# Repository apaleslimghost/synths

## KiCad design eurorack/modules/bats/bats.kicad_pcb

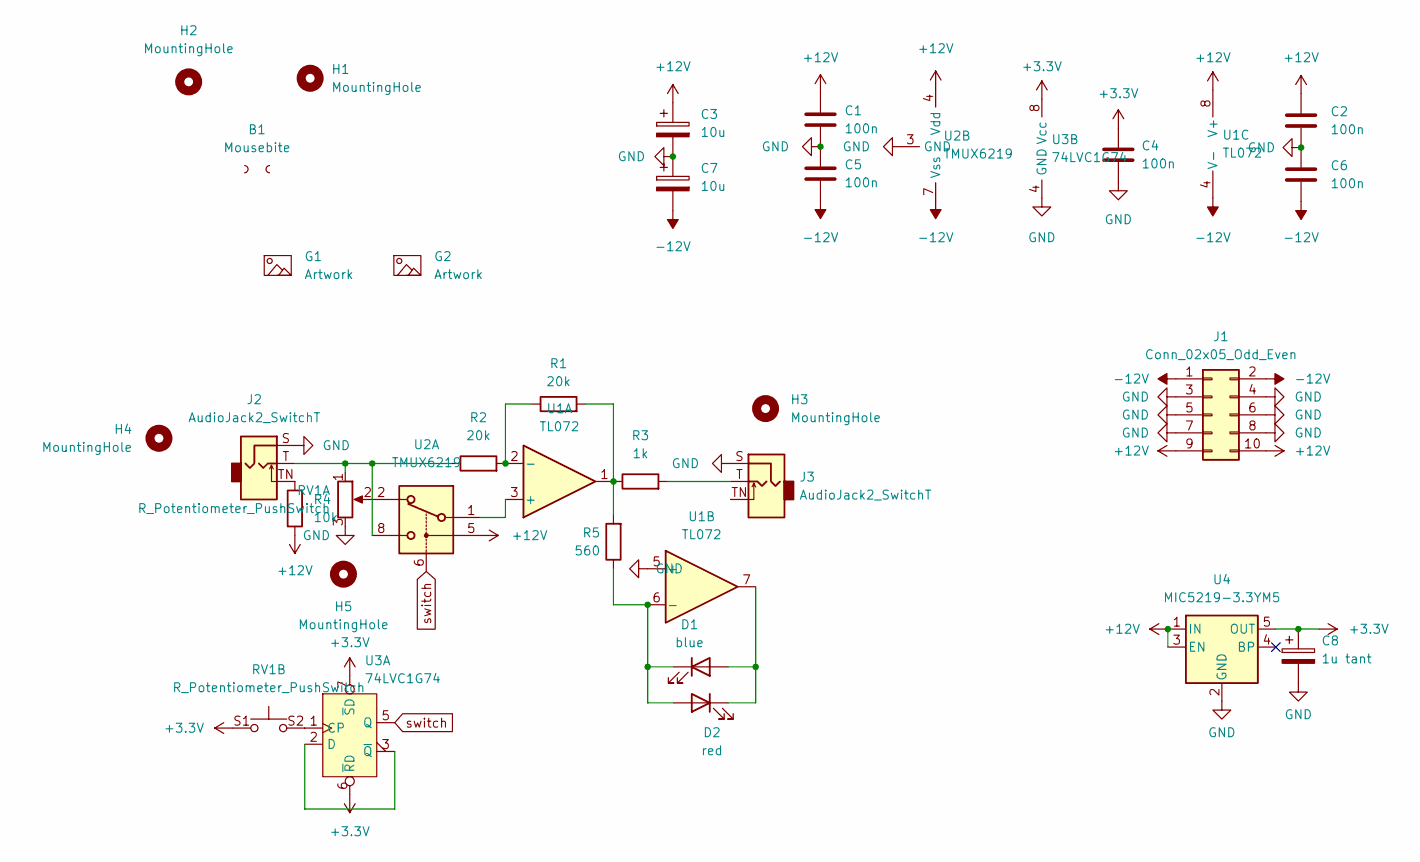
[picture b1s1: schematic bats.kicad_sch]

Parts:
B1: Mousebite; mousebite-2.54x5.08mm
C1, C2, C4, C5, C6: 100n; C_0805_2012Metric_Pad1.18x1.45mm_HandSolder
C3, C7: 10u; CP_EIA-3216-18_Kemet-A_Pad1.58x1.35mm_HandSolder
C8: 1u tant; CP_EIA-3216-18_Kemet-A_Pad1.58x1.35mm_HandSolder
D1: blue; LED_0805_2012Metric_Pad1.15x1.40mm_HandSolder
D2: red; LED_0805_2012Metric_Pad1.15x1.40mm_HandSolder
G1, G2: Artwork
H1, H2: MountingHole; eurorack panel mounting slot
H3, H4: MountingHole; hole 6mm (jack panel)
H5: MountingHole; hole 6.5mm (potentiometer panel)
J1: Conn_02x05_Odd_Even; PinHeader_2x05_P2.54mm_Vertical_SMD
J2, J3: AudioJack2_SwitchT; Jack_3.5mm_QingPu_WQP-PJ398SM_Vertical
R1, R2: 20k; R_0805_2012Metric_Pad1.20x1.40mm_HandSolder
R3: 1k; R_0805_2012Metric_Pad1.20x1.40mm_HandSolder
R4: 10k; R_0805_2012Metric_Pad1.20x1.40mm_HandSolder
R5: 560; R_0805_2012Metric_Pad1.20x1.40mm_HandSolder
RV1: R_Potentiometer_PushSwitch; PRS11R Momentary Switch Potentiometer; Part # P170SP1-QC15BR10K
U1: TL072; SOT-23-8_Handsoldering
U2: TMUX6219; VSSOP-8_3.0x3.0mm_P0.65mm
U3: 74LVC1G74; SSOP-8_2.95x2.8mm_P0.65mm
U4: MIC5219-3.3YM5; SOT-23-5

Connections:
+3.3V: C4.1, C8.1, RV1.S1, U3.6 (~RD), U3.7 (~SD), U3.8 (Vcc), U4.5 (OUT)
+12V: C1.1, C2.1, C3.1, J1.9, J1.10, R4.1, U1.8 (V+), U2.4 (Vdd), U2.5, U4.1 (IN), U4.3 (EN)
-12V: C5.2, C6.2, C7.2, J1.1, J1.2, U1.4 (V-), U2.7 (Vss)
GND: C1.2, C2.2, C3.2, C4.2, C5.1, C6.1, C7.1, C8.2, J1.3, J1.4, J1.5, J1.6, J1.7, J1.8, J2.S, J3.S, RV1.3, U1.5 (+), U2.3 (GND), U3.4 (GND), U4.2 (GND)
unnamed: D1.1 (K), D2.2 (A), R5.1, U1.6 (-)
unnamed: D1.2 (A), D2.1 (K), U1.7
unnamed: J2.T, R2.1, RV1.1, U2.8
unnamed: J2.TN, R4.2
unnamed: J3.T, R3.2
unnamed: R1.1, R2.2, U1.2 (-)
unnamed: R1.2, R3.1, R5.2, U1.1
unnamed: RV1.2, U2.2
unnamed: RV1.S2, U3.1 (CP)
unnamed: U1.3 (+), U2.1
unnamed: U3.2 (D), U3.3 (~Q)
switch: U2.6, U3.5 (Q)

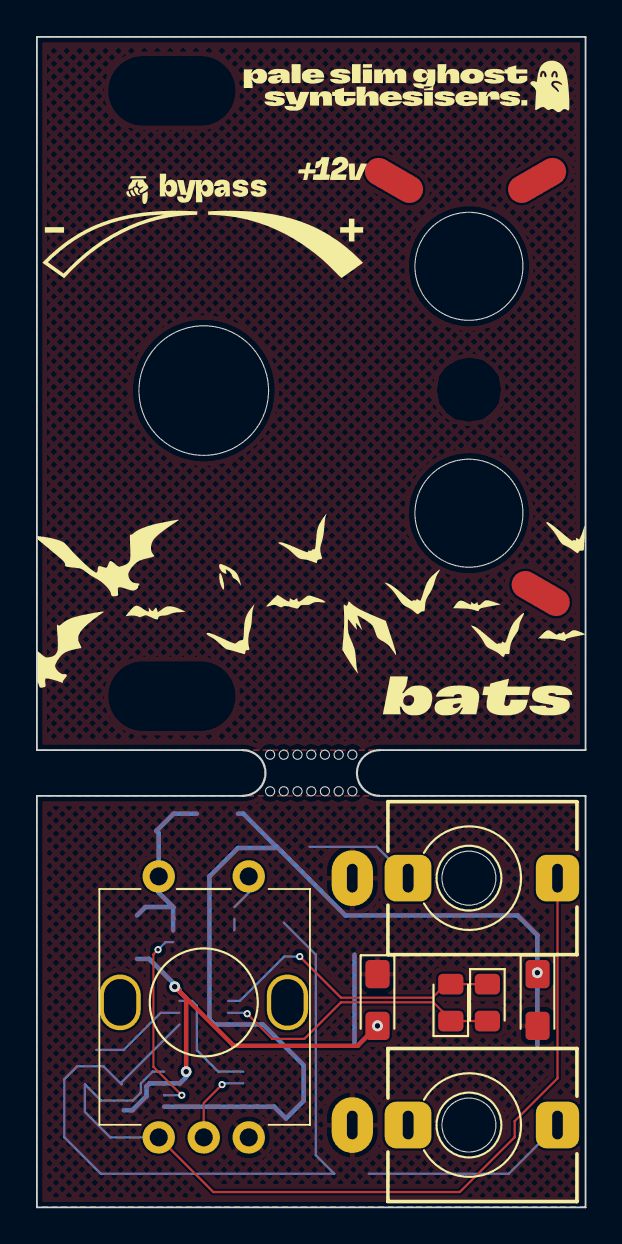
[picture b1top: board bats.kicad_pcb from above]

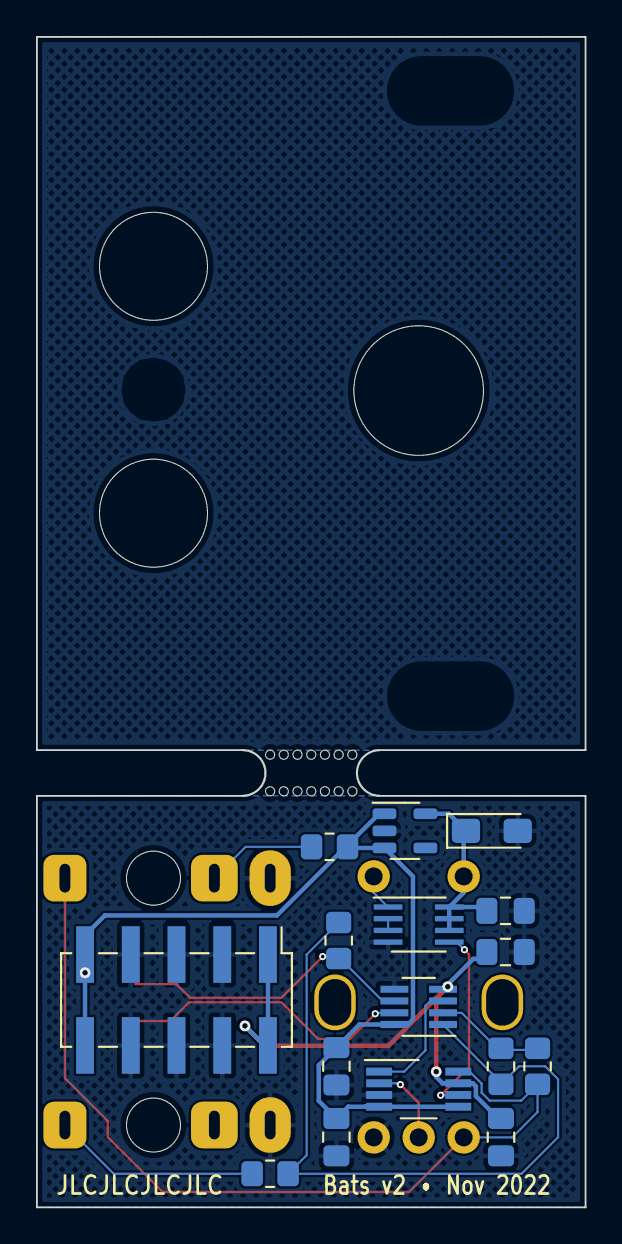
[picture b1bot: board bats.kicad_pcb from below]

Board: 2 copper layers, 30.5 x 65.0 mm, 31 parts (16 on the bottom side), 16 nets.

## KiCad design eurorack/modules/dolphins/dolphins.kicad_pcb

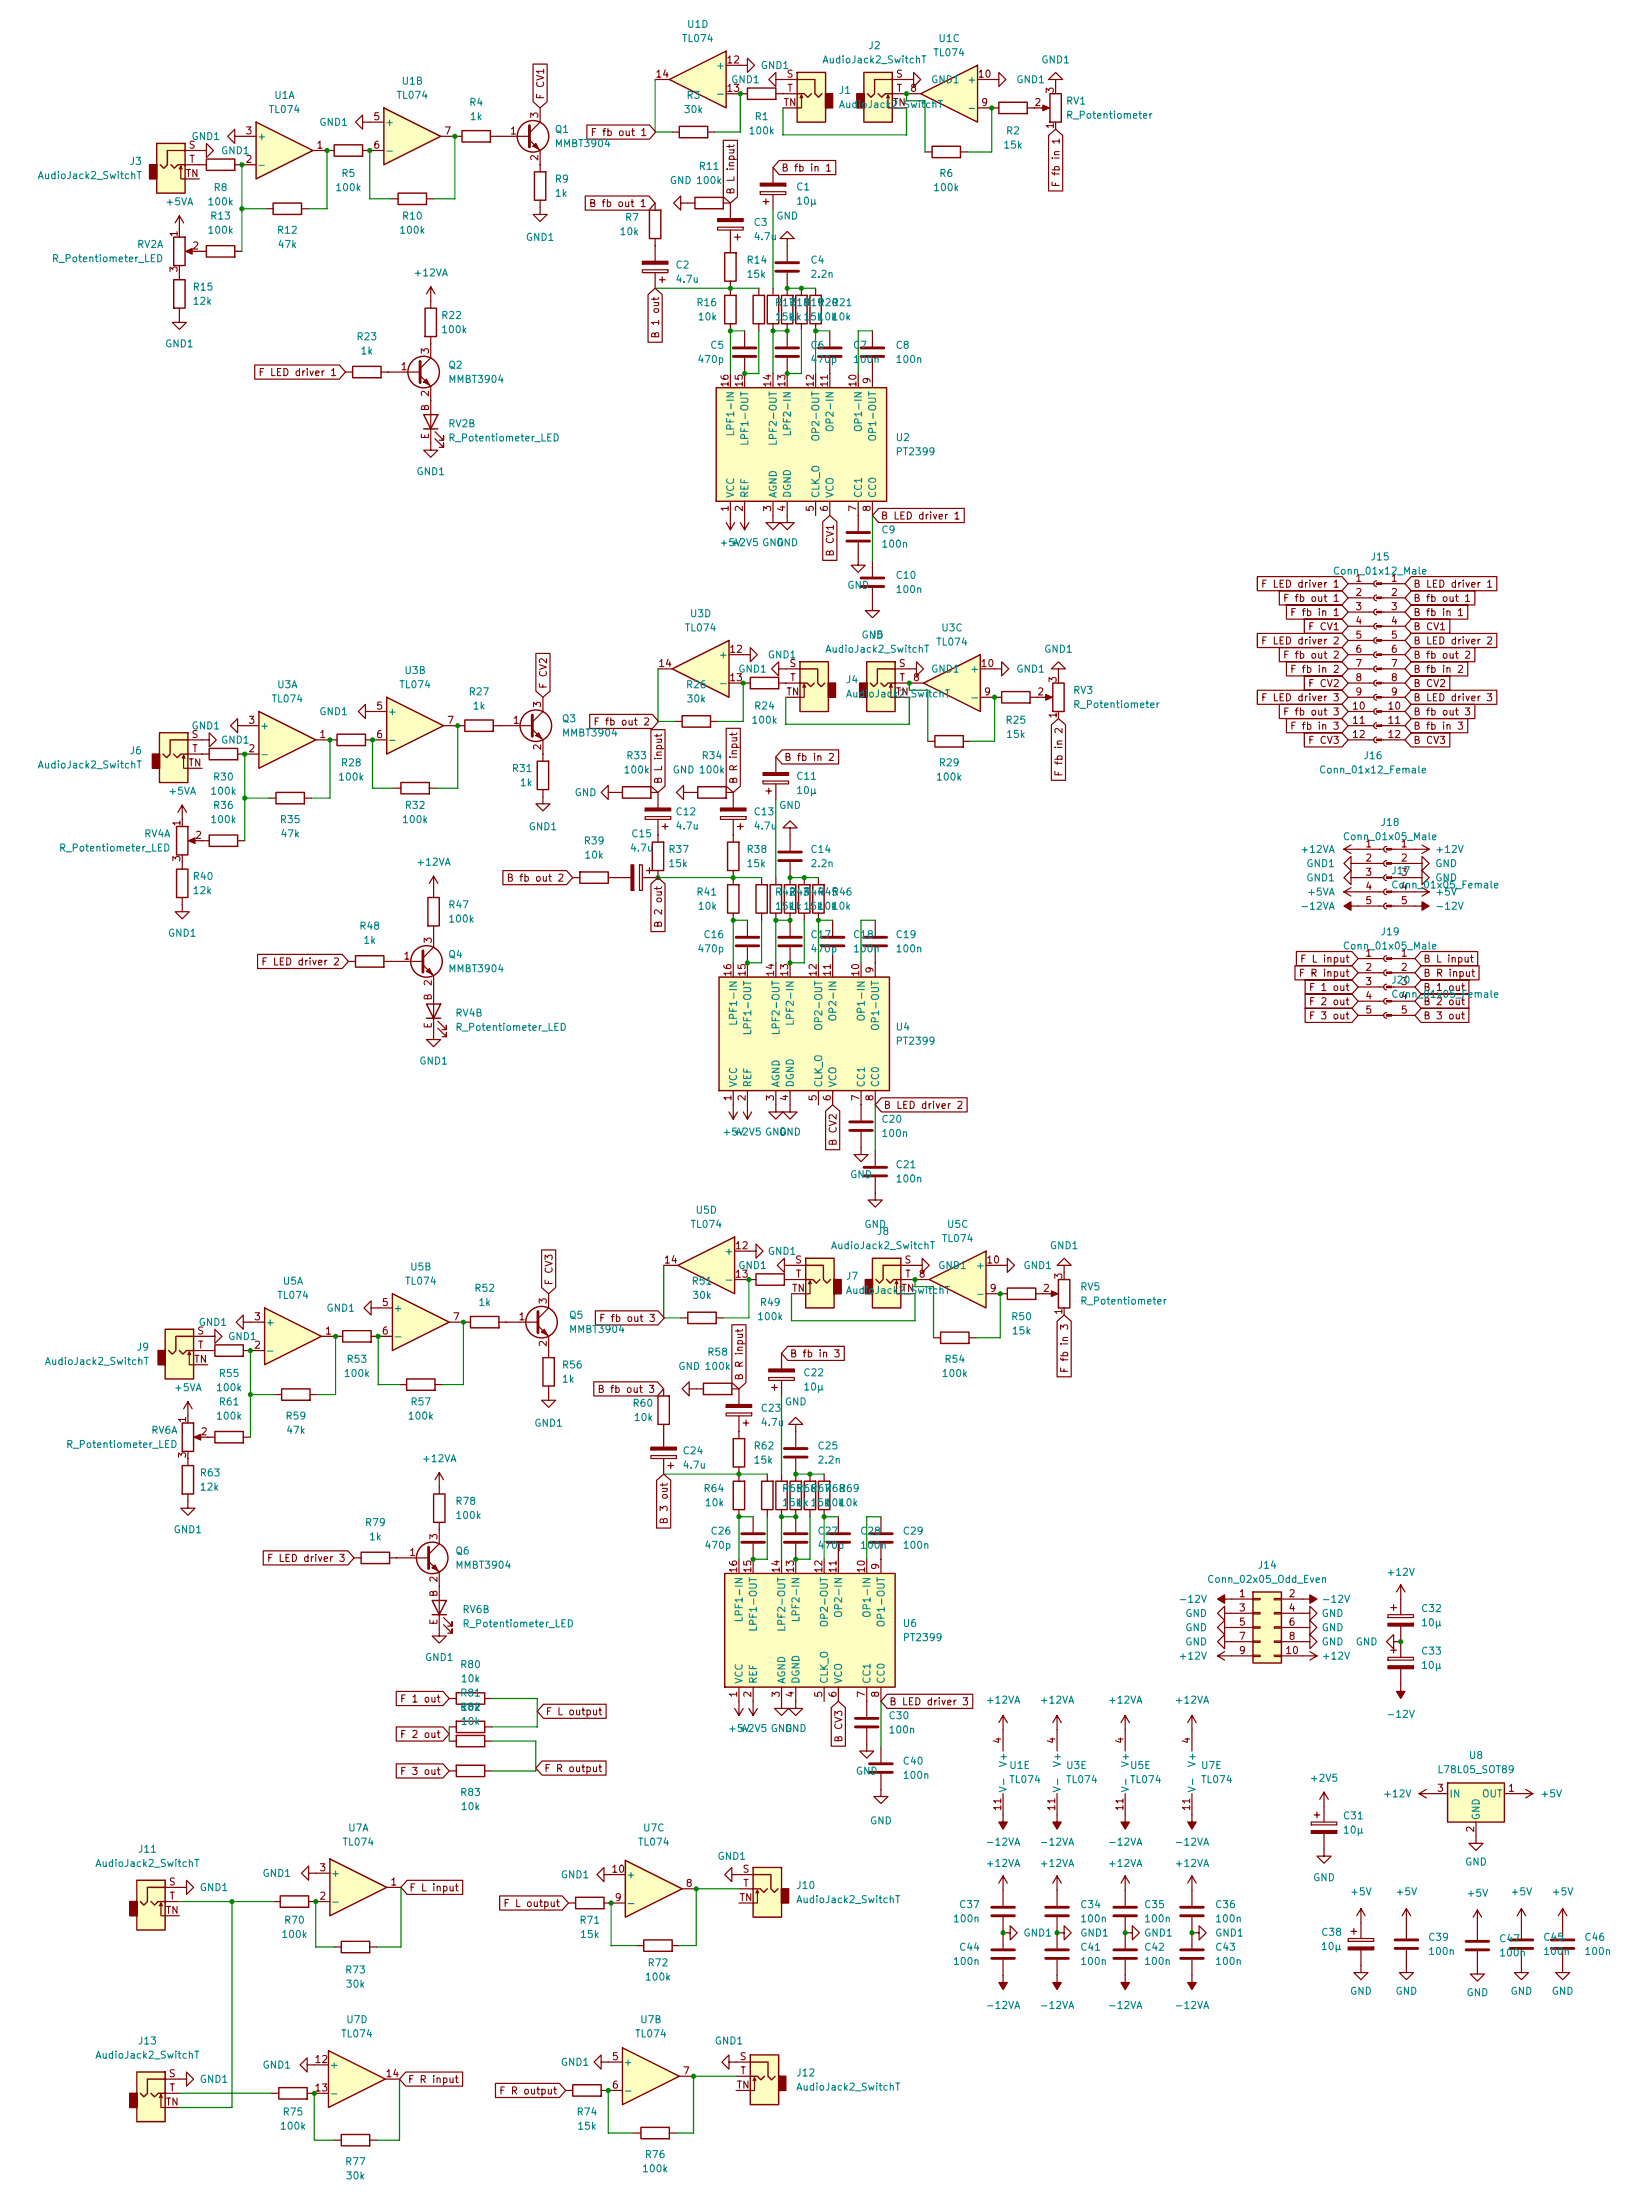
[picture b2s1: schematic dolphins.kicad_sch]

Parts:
C1, C11, C22, C32, C33, C38: 10μ; CP_Elec_5x5.9
C2, C3, C12, C13, C15, C23, C24: 4.7u; CP_Elec_5x5.9
C4, C14, C25: 2.2n; C_0805_2012Metric_Pad1.18x1.45mm_HandSolder
C5, C6, C16, C17, C26, C27: 470p; C_0805_2012Metric_Pad1.18x1.45mm_HandSolder
C7, C8, C9, C10, C18, C19, C20, C21, C28, C29, C30, C34, C35, C36, C37, C39, C40, C41, C42, C43, C44, C45, C46, C47: 100n; C_0805_2012Metric_Pad1.18x1.45mm_HandSolder
C31: 10μ; C_1210_3225Metric_Pad1.33x2.70mm_HandSolder
J1, J2, J3, J4, J5, J6, J7, J8, J9, J10, J11, J12, J13: AudioJack2_SwitchT; Jack_3.5mm_QingPu_WQP-PJ398SM_Vertical
J14: Conn_02x05_Odd_Even; PinHeader_Shrouded_2x05_P2.54mm_Horizontal
J15: Conn_01x12_Male; PinHeader_1x12_P2.54mm_Vertical
J16: Conn_01x12_Female; PinSocket_1x12_P2.54mm_Vertical
J17, J20: Conn_01x05_Female; PinSocket_1x05_P2.54mm_Vertical
J18, J19: Conn_01x05_Male; PinHeader_1x05_P2.54mm_Vertical
Q1, Q2, Q3, Q4, Q5, Q6: MMBT3904; SOT-23
R1, R5, R6, R8, R10, R11, R13, R22, R24, R28, R29, R30, R32, R33, R34, R36, R47, R49, R53, R54, R55, R57, R58, R61, R70, R72, R75, R76, R78: 100k; R_0805_2012Metric_Pad1.20x1.40mm_HandSolder
R2, R14, R17, R19, R25, R37, R38, R42, R44, R50, R62, R65, R67, R71, R74: 15k; R_0805_2012Metric_Pad1.20x1.40mm_HandSolder
R3, R26, R51, R73, R77: 30k; R_0805_2012Metric_Pad1.20x1.40mm_HandSolder
R4, R9, R18, R23, R27, R31, R43, R48, R52, R56, R66, R79: 1k; R_0805_2012Metric_Pad1.20x1.40mm_HandSolder
R7, R16, R20, R21, R39, R41, R45, R46, R60, R64, R68, R69, R80, R81, R82, R83: 10k; R_0805_2012Metric_Pad1.20x1.40mm_HandSolder
R12, R35, R59: 47k; R_0805_2012Metric_Pad1.20x1.40mm_HandSolder
R15, R40, R63: 12k; R_0805_2012Metric_Pad1.20x1.40mm_HandSolder
RV1, RV3, RV5: R_Potentiometer; Potentiometer_Song_Huei_R0904N
RV2, RV4, RV6: R_Potentiometer_LED; Alpha RA2045F-20
U1, U3, U5, U7: TL074; SOIC-14_3.9x8.7mm_P1.27mm
U2, U4, U6: PT2399; SOIC-16_3.9x9.9mm_P1.27mm
U8: L78L05_SOT89; SOT-89-3

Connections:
+2V5: C31.1, U2.2 (REF), U4.2 (REF), U6.2 (REF)
+5V: C38.1, C39.1, C45.1, C46.1, C47.1, J18.4, U2.1 (VCC), U4.1 (VCC), U6.1 (VCC), U8.1 (OUT)
+5VA: J17.4, RV2.1, RV4.1, RV6.1
+12V: C32.1, J14.9, J14.10, J18.1, U8.3 (IN)
+12VA: C34.1, C35.1, C36.1, C37.1, J17.1, R22.1, R47.1, R78.1, U1.4 (V+), U3.4 (V+), U5.4 (V+), U7.4 (V+); also elsewhere on the board
-12V: C33.2, J14.1, J14.2, J18.5
-12VA: C41.2, C42.2, C43.2, C44.2, J17.5, U1.11 (V-), U3.11 (V-), U5.11 (V-), U7.11 (V-); also elsewhere on the board
B 1 out: C2.1, J19.3, R14.1, R16.2, R17.2
B 2 out: C15.1, J19.4, R37.1, R38.1, R41.2, R42.2
B 3 out: C24.1, J19.5, R62.1, R64.2, R65.2
B CV1: J15.4, U2.6 (VCO)
B CV2: J15.8, U4.6 (VCO)
B CV3: J15.12, U6.6 (VCO)
B L input: C3.2, C12.2, J19.1, R11.2, R33.2
B LED driver 1: C10.1, J15.1, U2.8 (CC0)
B LED driver 2: C21.1, J15.5, U4.8 (CC0)
B LED driver 3: C40.1, J15.9, U6.8 (CC0)
B R input: C13.2, C23.2, J19.2, R34.2, R58.2
B fb in 1: C1.2, J15.3
B fb in 2: C11.2, J15.7
B fb in 3: C22.2, J15.11
B fb out 1: J15.2, R7.2
B fb out 2: J15.6, R39.2
B fb out 3: J15.10, R60.2
F 1 out: J20.3, R80.2
F 2 out: J20.4, R81.2, R82.2
F 3 out: J20.5, R83.2
F CV1: J16.4, Q1.3 (C)
F CV2: J16.8, Q3.3 (C)
F CV3: J16.12, Q5.3 (C)
F L input: J20.1, R73.2, U7.1
F L output: R71.1, R80.1, R81.1
F LED driver 1: J16.1, R23.1
F LED driver 2: J16.5, R48.1
F LED driver 3: J16.9, R79.1
F R input: J20.2, R77.2, U7.14
F R output: R74.1, R82.1, R83.1
F fb in 1: J16.3, RV1.1
F fb in 2: J16.7, RV3.1
F fb in 3: J16.11, RV5.1
F fb out 1: J16.2, R3.1, U1.14
F fb out 2: J16.6, R26.1, U3.14
F fb out 3: J16.10, R51.1, U5.14
GND: C4.1, C9.2, C10.2, C14.1, C20.2, C21.2, C25.1, C30.2, C31.2, C32.2, C33.1, C38.2, C39.2, C40.2, C45.2, C46.2, C47.2, J14.3, J14.4, J14.5, J14.6, J14.7, J14.8, J18.2, J18.3, R11.1, R33.1, R34.1, R58.1, U2.3 (AGND), U2.4 (DGND), U4.3 (AGND), U4.4 (DGND), U6.3 (AGND), U6.4 (DGND), U8.2 (GND)
GND1: C34.2, C35.2, C36.2, C37.2, C41.1, C42.1, C43.1, C44.1, J1.S, J2.S, J3.S, J4.S, J5.S, J6.S, J7.S, J8.S, J9.S, J10.S, J11.S, J12.S, J13.S, J17.2, J17.3, R9.1, R15.2, R31.1, R40.2, R56.1, R63.2, RV1.3, RV2.E, RV3.3, RV4.E, RV5.3, RV6.E, U1.3 (+), U1.5 (+), U1.10 (+), U1.12 (+), U3.3 (+), U3.5 (+), U3.10 (+), U3.12 (+), U5.3 (+), U5.5 (+), U5.10 (+), U5.12 (+), U7.3 (+), U7.5 (+), U7.10 (+), U7.12 (+); also elsewhere on the board
unnamed: C1.1, R18.2
unnamed: C2.2, R7.1
unnamed: C3.1, R14.2
unnamed: C4.2, R19.2, R20.2, R21.2
unnamed: C5.1, R16.1, U2.16 (LPF1-IN)
unnamed: C5.2, R17.1, U2.15 (LPF1-OUT)
unnamed: C6.1, R18.1, R19.1, U2.14 (LPF2-OUT)
unnamed: C6.2, R20.1, U2.13 (LPF2-IN)
unnamed: C7.1, R21.1, U2.12 (OP2-OUT)
unnamed: C7.2, U2.11 (OP2-IN)
unnamed: C8.1, U2.10 (OP1-IN)
unnamed: C8.2, U2.9 (OP1-OUT)
unnamed: C9.1, U2.7 (CC1)
unnamed: C11.1, R43.2
unnamed: C12.1, R37.2
unnamed: C13.1, R38.2
unnamed: C14.2, R44.2, R45.2, R46.2
unnamed: C15.2, R39.1
unnamed: C16.1, R41.1, U4.16 (LPF1-IN)
unnamed: C16.2, R42.1, U4.15 (LPF1-OUT)
unnamed: C17.1, R43.1, R44.1, U4.14 (LPF2-OUT)
unnamed: C17.2, R45.1, U4.13 (LPF2-IN)
unnamed: C18.1, R46.1, U4.12 (OP2-OUT)
unnamed: C18.2, U4.11 (OP2-IN)
unnamed: C19.1, U4.10 (OP1-IN)
unnamed: C19.2, U4.9 (OP1-OUT)
unnamed: C20.1, U4.7 (CC1)
unnamed: C22.1, R66.2
unnamed: C23.1, R62.2
unnamed: C24.2, R60.1
unnamed: C25.2, R67.2, R68.2, R69.2
unnamed: C26.1, R64.1, U6.16 (LPF1-IN)
unnamed: C26.2, R65.1, U6.15 (LPF1-OUT)
unnamed: C27.1, R66.1, R67.1, U6.14 (LPF2-OUT)
unnamed: C27.2, R68.1, U6.13 (LPF2-IN)
unnamed: C28.1, R69.1, U6.12 (OP2-OUT)
unnamed: C28.2, U6.11 (OP2-IN)
unnamed: C29.1, U6.10 (OP1-IN)
unnamed: C29.2, U6.9 (OP1-OUT)
unnamed: C30.1, U6.7 (CC1)
unnamed: J1.T, R1.2
unnamed: J1.TN, J2.TN
unnamed: J2.T, R6.1, U1.8
unnamed: J3.T, R8.1
unnamed: J4.T, R24.2
unnamed: J4.TN, J5.TN
unnamed: J5.T, R29.1, U3.8
unnamed: J6.T, R30.1
unnamed: J7.T, R49.2
unnamed: J7.TN, J8.TN
unnamed: J8.T, R54.1, U5.8
unnamed: J9.T, R55.1
unnamed: J10.T, R72.2, U7.8
unnamed: J11.T, J13.TN, R70.1
unnamed: J12.T, R76.2, U7.7
unnamed: J13.T, R75.1
unnamed: Q1.1 (B), R4.2
unnamed: Q1.2 (E), R9.2
unnamed: Q2.1 (B), R23.2
unnamed: Q2.2 (E), RV2.B
unnamed: Q2.3 (C), R22.2
unnamed: Q3.1 (B), R27.2
unnamed: Q3.2 (E), R31.2
unnamed: Q4.1 (B), R48.2
unnamed: Q4.2 (E), RV4.B
unnamed: Q4.3 (C), R47.2
unnamed: Q5.1 (B), R52.2
unnamed: Q5.2 (E), R56.2
unnamed: Q6.1 (B), R79.2
unnamed: Q6.2 (E), RV6.B
unnamed: Q6.3 (C), R78.2
unnamed: R1.1, R3.2, U1.13 (-)
unnamed: R2.1, R6.2, U1.9 (-)
unnamed: R2.2, RV1.2
unnamed: R5.2, R10.1, U1.6 (-)
unnamed: R4.1, R10.2, U1.7
unnamed: R8.2, R12.1, R13.2, U1.2 (-)
unnamed: R5.1, R12.2, U1.1
unnamed: R13.1, RV2.2
unnamed: R15.1, RV2.3
unnamed: R24.1, R26.2, U3.13 (-)
unnamed: R25.1, R29.2, U3.9 (-)
unnamed: R25.2, RV3.2
unnamed: R27.1, R32.2, U3.7
unnamed: R28.1, R35.2, U3.1
unnamed: R28.2, R32.1, U3.6 (-)
unnamed: R30.2, R35.1, R36.2, U3.2 (-)
unnamed: R36.1, RV4.2
unnamed: R40.1, RV4.3
unnamed: R49.1, R51.2, U5.13 (-)
unnamed: R50.1, R54.2, U5.9 (-)
unnamed: R50.2, RV5.2
unnamed: R52.1, R57.2, U5.7
unnamed: R53.1, R59.2, U5.1
unnamed: R53.2, R57.1, U5.6 (-)
unnamed: R55.2, R59.1, R61.2, U5.2 (-)
unnamed: R61.1, RV6.2
unnamed: R63.1, RV6.3
unnamed: R70.2, R73.1, U7.2 (-)
unnamed: R71.2, R72.1, U7.9 (-)
unnamed: R74.2, R76.1, U7.6 (-)
unnamed: R75.2, R77.1, U7.13 (-)

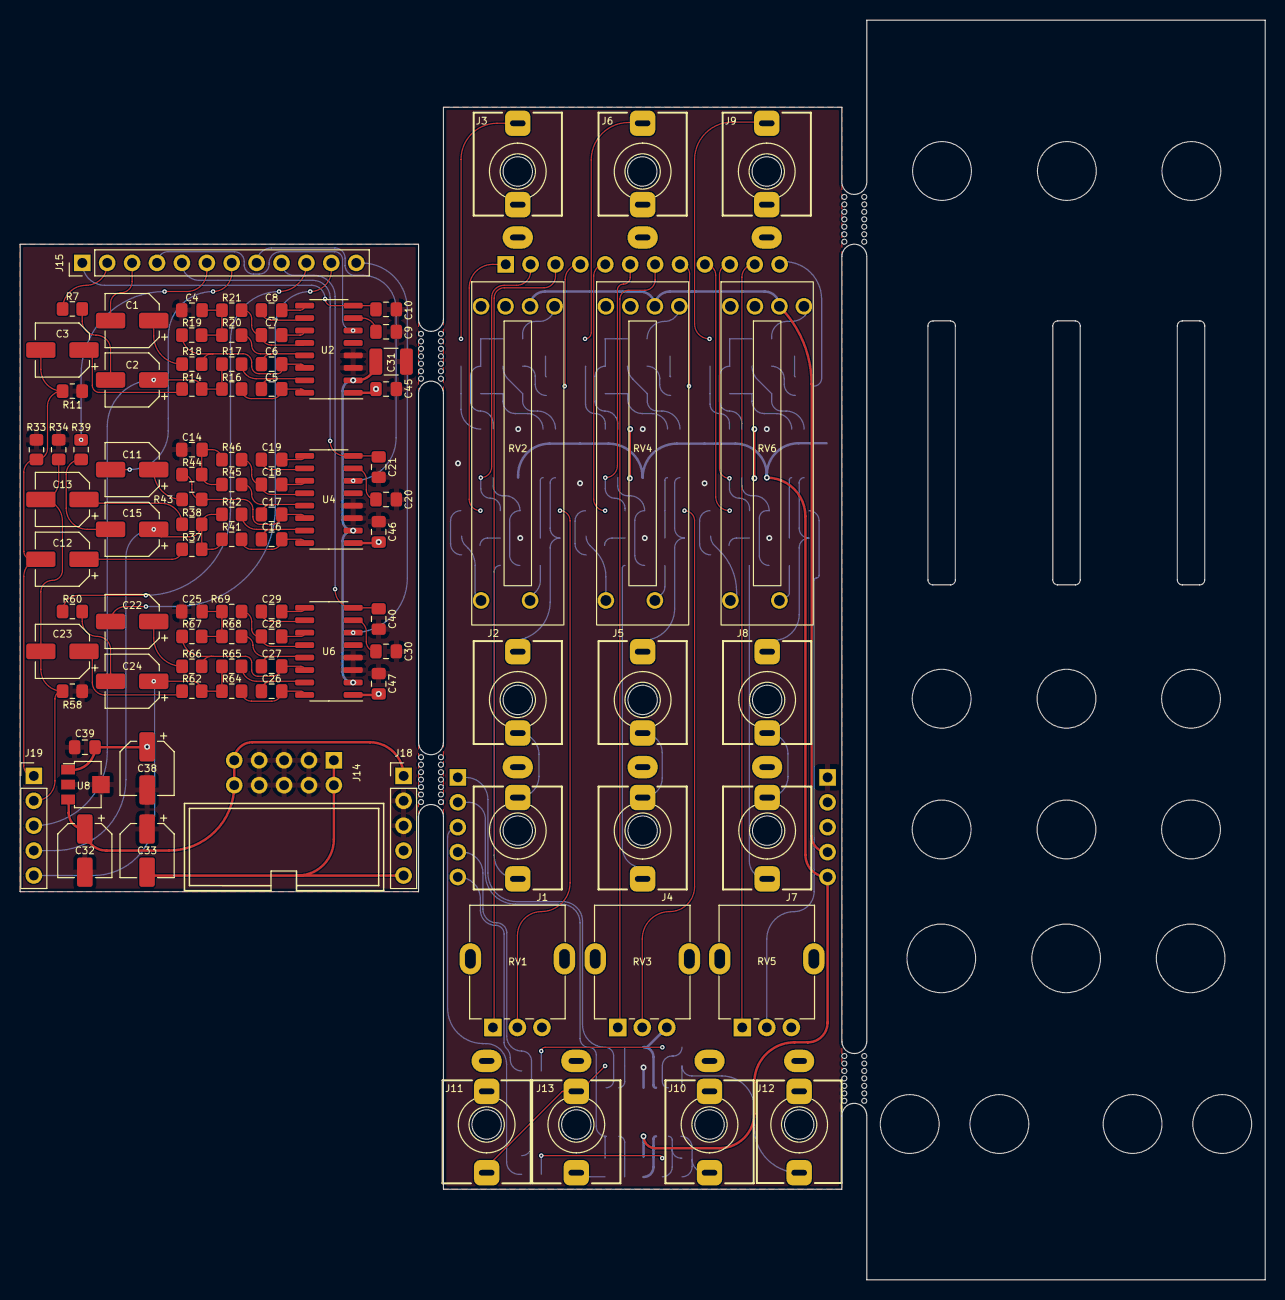
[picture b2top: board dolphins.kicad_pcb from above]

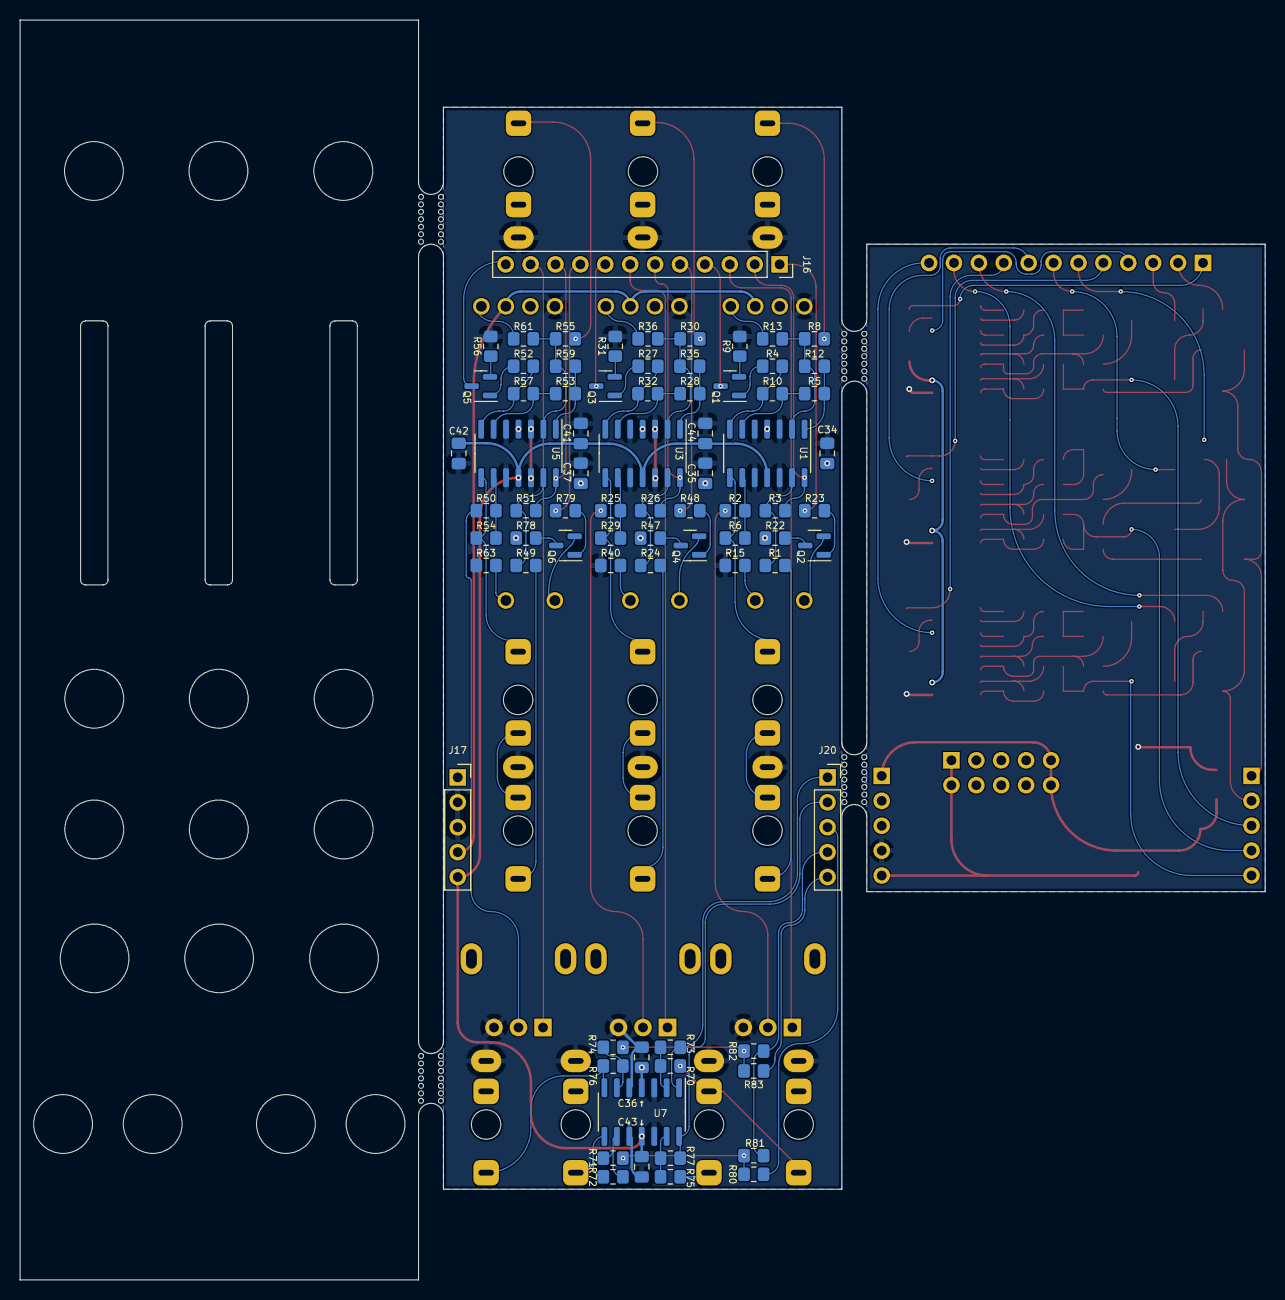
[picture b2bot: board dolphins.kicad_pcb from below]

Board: 2 copper layers, 127.0 x 128.5 mm, 174 parts (75 on the bottom side), 147 nets.

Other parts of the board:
C36↑, C43↓: 100n; C_0805_2012Metric_Pad1.18x1.45mm_HandSolder
mouse-bite-2mm-slot, mouse-bite-2mm-slot#2, mouse-bite-2mm-slot#3, mouse-bite-2mm-slot#4: VAL**; mousebite-2.54x5.08mm

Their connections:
+12VA: C36↑.1; also elsewhere on the board
-12VA: C43↓.2; also elsewhere on the board
GND1: C36↑.2, C43↓.1; also elsewhere on the board

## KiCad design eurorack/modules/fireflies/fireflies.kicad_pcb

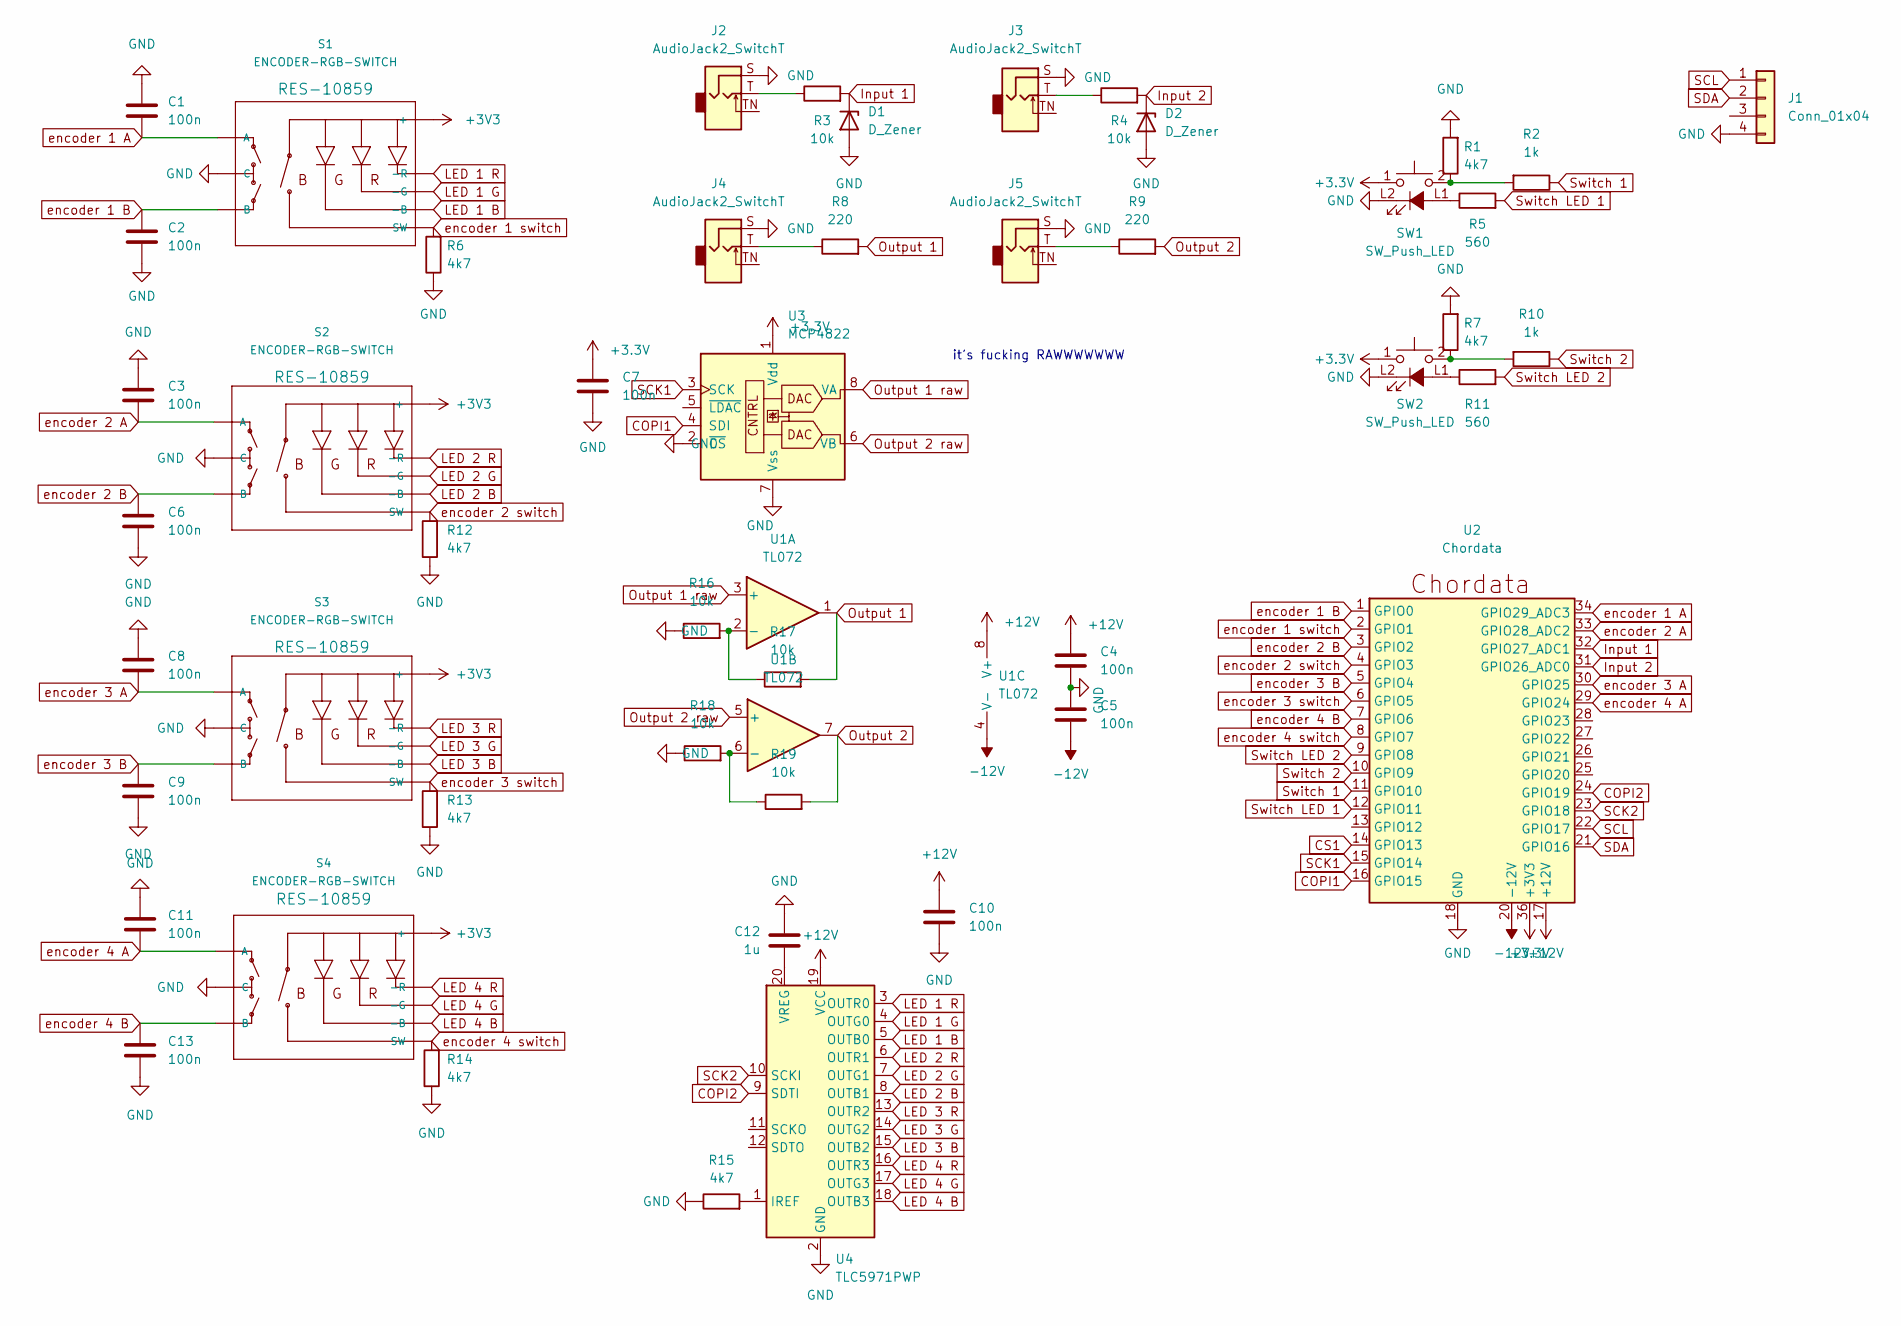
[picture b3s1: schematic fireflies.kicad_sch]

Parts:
C1, C2, C3, C4, C5, C6, C7, C8, C9, C10, C11, C13: 100n; C_0805_2012Metric_Pad1.18x1.45mm_HandSolder
C12: 1u; C_0805_2012Metric_Pad1.18x1.45mm_HandSolder
D1, D2: D_Zener; D_0805_2012Metric_Pad1.15x1.40mm_HandSolder
J1: Conn_01x04; Stemma QT Qwiic JST_SH_SM04B
J2, J3, J4, J5: AudioJack2_SwitchT; Jack_3.5mm_QingPu_WQP-PJ398SM_Vertical
R1, R6, R7, R12, R13, R14, R15: 4k7; R_0805_2012Metric_Pad1.20x1.40mm_HandSolder
R2, R10: 1k; R_0805_2012Metric_Pad1.20x1.40mm_HandSolder
R3, R4, R16, R17, R18, R19: 10k; R_0805_2012Metric_Pad1.20x1.40mm_HandSolder
R5, R11: 560; R_0805_2012Metric_Pad1.20x1.40mm_HandSolder
R8, R9: 220; R_0805_2012Metric_Pad1.20x1.40mm_HandSolder
S1, S2, S3, S4: ENCODER-RGB-SWITCH; ENCODER_LED_3
SW1, SW2: SW_Push_LED; PB01-109TL
U1: TL072
U2: Chordata
U3: MCP4822; MSOP-8_3x3mm_P0.65mm
U4: TLC5971PWP; HTSSOP-20-1EP_4.4x6.5mm_P0.65mm_EP3.4x6.5mm_Mask2.75x3.43mm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

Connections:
+12V: C4.2, C10.2, U1.8 (V+), U2.17 (+12V), U4.19 (VCC)
-12V: C5.1, U1.4 (V-), U2.20 (-12V)
COPI1: U2.16 (GPIO15), U3.4 (SDI)
COPI2: U2.24 (GPIO19), U4.9 (SDTI)
CS1: U2.14 (GPIO13)
GND: C1.1, C2.2, C3.1, C4.1, C5.2, C6.2, C7.1, C8.1, C9.2, C10.1, C11.1, C12.2, C13.2, D1.2 (A), D2.2 (A), J1.4, J2.S, J3.S, J4.S, J5.S, R1.2, R6.1, R7.2, R12.1, R13.1, R14.1, R15.1, R16.1, R18.1, S1.C, S2.C, S3.C, S4.C, SW1.L2 (K), SW2.L2 (K), U2.18 (GND), U2.19 (GND), U2.35 (GND), U3.2 (~CS), U3.7 (Vss), U4.2 (GND), U4.21 (GND)
Input 1: D1.1 (K), R3.2, U2.32 (GPIO27_ADC1)
Input 2: D2.1 (K), R4.2, U2.31 (GPIO26_ADC0)
LED 1 B: S1.4 (-B), U4.5 (OUTB0)
LED 1 G: S1.2 (-G), U4.4 (OUTG0)
LED 1 R: S1.1 (-R), U4.3 (OUTR0)
LED 2 B: S2.4 (-B), U4.8 (OUTB1)
LED 2 G: S2.2 (-G), U4.7 (OUTG1)
LED 2 R: S2.1 (-R), U4.6 (OUTR1)
LED 3 B: S3.4 (-B), U4.15 (OUTB2)
LED 3 G: S3.2 (-G), U4.14 (OUTG2)
LED 3 R: S3.1 (-R), U4.13 (OUTR2)
LED 4 B: S4.4 (-B), U4.18 (OUTB3)
LED 4 G: S4.2 (-G), U4.17 (OUTG3)
LED 4 R: S4.1 (-R), U4.16 (OUTR3)
unnamed: C12.1, U4.20 (VREG)
unnamed: J2.T, R3.1
unnamed: J3.T, R4.1
unnamed: J4.T, R8.1
unnamed: J5.T, R9.1
unnamed: R1.1, R2.2, SW1.2
unnamed: R5.1, SW1.L1 (A)
unnamed: R7.1, R10.2, SW2.2
unnamed: R11.1, SW2.L1 (A)
unnamed: R15.2, U4.1 (IREF)
unnamed: R16.2, R17.1, U1.2 (-)
unnamed: R18.2, R19.1, U1.6 (-)
Output 1: R8.2, R17.2, U1.1
Output 1 raw: U1.3 (+), U3.8 (VA)
Output 2: R9.2, R19.2, U1.7
Output 2 raw: U1.5 (+), U3.6 (VB)
SCK1: U2.15 (GPIO14), U3.3 (SCK)
SCK2: U2.23 (GPIO18), U4.10 (SCKI)
SCL: J1.1, U2.22 (GPIO17)
SDA: J1.2, U2.21 (GPIO16)
Switch 1: R2.1, U2.11 (GPIO10)
Switch 2: R10.1, U2.10 (GPIO9)
Switch LED 1: R5.2, U2.12 (GPIO11)
Switch LED 2: R11.2, U2.9 (GPIO8)
encoder 1 A: C1.2, S1.A, U2.34 (GPIO29_ADC3)
encoder 1 B: C2.1, S1.B, U2.1 (GPIO0)
encoder 1 switch: R6.2, S1.3 (SW), U2.2 (GPIO1)
encoder 2 A: C3.2, S2.A, U2.33 (GPIO28_ADC2)
encoder 2 B: C6.1, S2.B, U2.3 (GPIO2)
encoder 2 switch: R12.2, S2.3 (SW), U2.4 (GPIO3)
encoder 3 A: C8.2, S3.A, U2.30 (GPIO25)
encoder 3 B: C9.1, S3.B, U2.5 (GPIO4)
encoder 3 switch: R13.2, S3.3 (SW), U2.6 (GPIO5)
encoder 4 A: C11.2, S4.A, U2.29 (GPIO24)
encoder 4 B: C13.1, S4.B, U2.7 (GPIO6)
encoder 4 switch: R14.2, S4.3 (SW), U2.8 (GPIO7)

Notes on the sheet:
it's fucking RAWWWWWWW

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
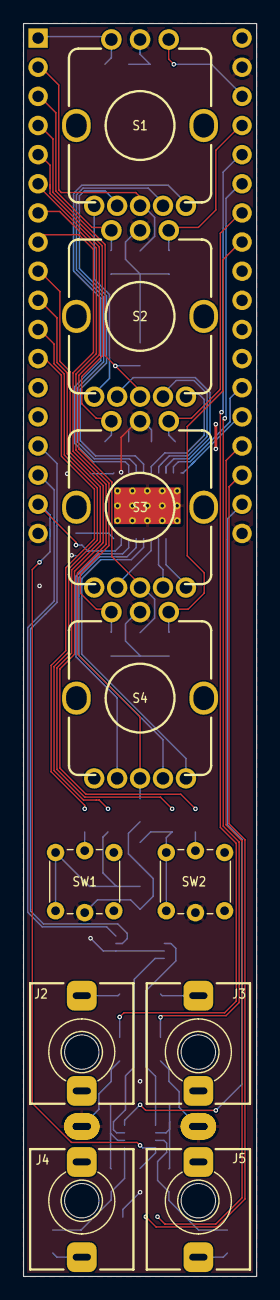
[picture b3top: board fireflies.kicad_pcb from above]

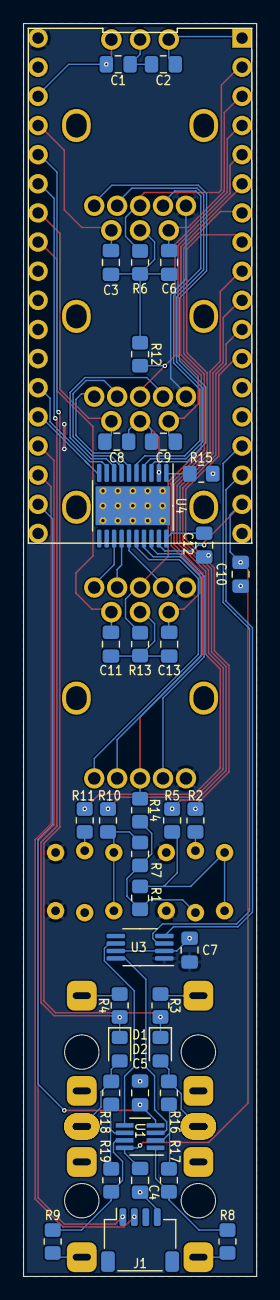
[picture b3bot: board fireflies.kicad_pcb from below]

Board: 2 copper layers, 20.3 x 109.2 mm, 49 parts (39 on the bottom side), 56 nets.
